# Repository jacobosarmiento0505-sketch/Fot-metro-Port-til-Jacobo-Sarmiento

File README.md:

# Fotómetro portátil para análisis de muestras

Proyecto del curso **Electrónica para Ingeniería Biomédica** (UDD) — diseño y
construcción de un fotómetro portátil de bajo costo, basado en un sensor de
color digital I2C y un microcontrolador ESP32, con pantalla OLED para
lectura directa de resultados.

## Estado del proyecto

- **Parte I** — propuesta, objetivos, requerimientos, diagrama de bloques y
  plan de pruebas: entregada (ver `docs/informes/`).
- **Parte II** — esquemático y layout de PCB en KiCad, lista de materiales
  (BOM) y archivos de fabricación: contenido de este repositorio.

## Resumen del hardware

El equipo mide la absorbancia/color de una muestra usando un sensor de
color RGB+Clear por I2C (**TCS34725**, módulo breakout HW-393), controlado
por una placa de desarrollo **ESP32**. Los resultados se muestran en una
pantalla **OLED SSD1306 (I2C, 128x64)**. Dos pulsadores permiten calibrar
con un blanco de referencia y disparar una medición. La alimentación es por
batería Li-Po, con carga/boost mediante un módulo TP4056 + convertidor
5V, regulado a 3.3V por el propio módulo ESP32.

> **Cambio de diseño respecto a la Parte I:** el front-end analógico
> original (fotodiodo BPW34 + amplificador operacional LM324) fue
> reemplazado por el sensor digital TCS34725, por sugerencia de los
> profesores del curso, para simplificar el diseño electrónico y de
> firmware. El detalle de este cambio está documentado en
> `docs/informes/`.

## Estructura del repositorio

```
.
├── README.md
├── LICENSE
├── docs/
│   ├── datasheets/      # hojas de datos de los componentes usados
│   ├── bitacora.md      # bitácora de avance del proyecto
│   └── informes/        # informes entregables (Parte I, Parte II)
├── electronica/
│   ├── kicad/           # proyecto KiCad: esquemático (.kicad_sch) y PCB (.kicad_pcb)
│   ├── libraries/       # librerías/símbolos o footprints propios (si los hay)
│   └── outputs/         # archivos de fabricación exportados (gerbers, STEP, BOM, PDFs)
├── firmware/            # firmware del ESP32 (Arduino/ESP-IDF)
└── software/            # software de apoyo (análisis de datos, scripts, etc.)
```

## Abrir el proyecto en KiCad

1. Instalar [KiCad 7](https://www.kicad.org/download/) (o superior).
2. Abrir `electronica/kicad/fotometro.kicad_pro`.
3. El esquemático (`fotometro.kicad_sch`) y el layout de PCB
   (`fotometro.kicad_pcb`) se abren desde ahí.

### Estado del enrutado de la PCB

La placa es de **una sola cara (B.Cu)**, pistas y espacios mínimos de
**0.8 mm**, con 4 orificios de montaje M3 (3.2 mm) — según lo pedido por el
Anexo 2 del enunciado. El esquemático está limpio (conectividad verificada
con `kicad-cli sch export netlist`) y la ubicación de todos los
footprints respeta los espaciamientos mínimos.

La placa se **rediseñó más compacta** a partir de la retroalimentación del
profesor: pasó de ~175 x 220 mm (38.500 mm²) a **~117 x 77 mm
(~9.000 mm²)**, cerca de la cuarta parte del área anterior. La distribución
se obtuvo con una búsqueda automática (recocido simulado sobre la ubicación y
rotación de cada componente, evaluando el ruteo real con el router A* del
proyecto). Las pistas se generaron con ese router y luego el estudiante las
**suavizó y ajustó a mano en KiCad** (pistas rectas y a 45°, sin zigzag); al final
se corrigieron unos pocos tramos de GND y VCC_5V para cumplir los 0,8 mm.

Resultado del enrutado (verificado sobre el archivo guardado):

- **Las 40 conexiones están ruteadas** — 0 pines sin conectar.
- **0 cortocircuitos** y **0 violaciones de separación**: el DRC con las reglas de
  0,8 mm de ancho y 0,8 mm de separación no marca errores.
- Todas las pistas están en **B.Cu** (0 en F.Cu), de 0,8 mm de ancho.
- Queda **1 advertencia** `copper_sliver` (B.Cu), documentada en el informe.
- Serigrafía con nombre del proyecto, versión (v2.0), equipo, integrantes,
  leyenda de pines de J1–J5 y pin 1 como pad cuadrado.

Cambio de huella: el interruptor SW1 pasó a `SW_Slide-03_Wuerth-WS-SLTV_10x2.5x6.4_P2.54mm`
(pines a 2.54 mm; el CK OS102011MS2Q anterior tenía pads a solo 2 mm entre sí, lo
que incumple por sí solo los 0.8 mm de separación). En el esquemático el pin 1 de SW1
es el contacto común (centro de la huella) y el pin 2 la salida.

## Archivos de fabricación

En `electronica/outputs/` se incluyen:

- `gerbers/` — Gerbers de las capas usadas + archivo de taladro (`.drl`)
- `fotometro_gerbers_y_taladro.zip` — Gerbers y taladro comprimidos
- `fotometro.step` — modelo 3D de la placa
- `fotometro_pcb.pdf` / `.svg` — vistas de la placa en vectorial
- `fotometro_pcb_cara_superior.png`, `fotometro_pcb_cara_inferior.png`,
  `fotometro_vista3d.png`, `fotometro_drc.png` — imágenes de las vistas y del DRC
- `fotometro_sch.pdf` / `fotometro_sch-1.png` — esquemático
- `BOM_fotometro.csv` — lista de materiales

Las bibliotecas propias están en `electronica/libraries/` y las hojas de datos
en `docs/datasheets/`. Los scripts que generan el esquemático y la PCB están en
`electronica/kicad/scripts/`.

## Autoría y uso de IA

Este repositorio fue preparado con ayuda de Claude (Anthropic) como asistente
de diseño: generación programática del esquemático y PCB en KiCad a partir
de la lista de materiales y topología de conexiones definidas por el
estudiante, además de la documentación. El detalle de este uso se describe
en `docs/informes/`, según lo pedido por el enunciado de la Parte II.

## Licencia

Este proyecto se publica bajo licencia MIT — ver [`LICENSE`](LICENSE).

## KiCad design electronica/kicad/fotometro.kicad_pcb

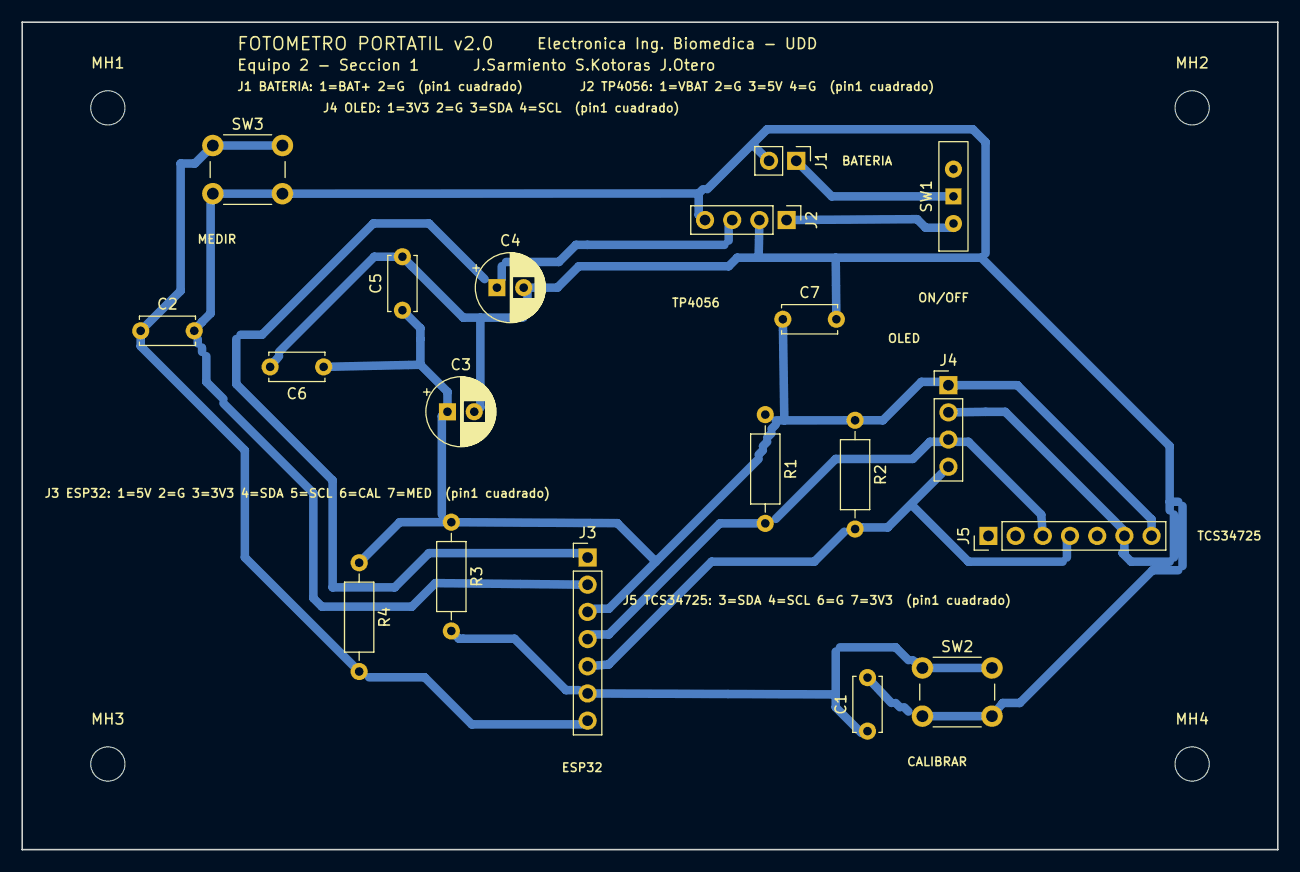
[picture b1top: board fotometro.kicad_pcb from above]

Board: 2 copper layers, 117.3 x 77.3 mm, 23 parts (0 on the bottom side), 9 nets.

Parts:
C1, C2, C5, C6, C7: 100nF; C_Disc_D5.0mm_W2.5mm_P5.00mm
C3, C4: 100uF; CP_Radial_D6.3mm_P2.50mm
J1: Bateria Li-Po; PinHeader_1x02_P2.54mm_Vertical
J2: TP4056+Boost5V; PinHeader_1x04_P2.54mm_Vertical
J3: ESP32; PinHeader_1x07_P2.54mm_Vertical
J4: OLED SSD1306; PinHeader_1x04_P2.54mm_Vertical
J5: TCS34725; PinHeader_1x07_P2.54mm_Vertical
MH1, MH2, MH3, MH4: MountingHole_3.2mm_M3
R1, R2: 4.7k; R_Axial_DIN0207_L6.3mm_D2.5mm_P10.16mm_Horizontal
R3, R4: 10k; R_Axial_DIN0207_L6.3mm_D2.5mm_P10.16mm_Horizontal
SW1: Interruptor encendido; SW_Slide-03_Wuerth-WS-SLTV_10x2.5x6.4_P2.54mm
SW2: CALIBRAR; SW_PUSH_6mm
SW3: MEDIR; SW_PUSH_6mm

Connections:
BAT_RAW: J1.1, SW1.1
GND: C1.2, C2.2, C3.2, C4.2, C5.2, C6.2, C7.2, J1.2, J2.2, J2.4, J3.2, J4.2, J5.6, SW2.2, SW3.2
GPIO_CAL: C1.1, J3.6, R3.2, SW2.1
GPIO_MED: C2.1, J3.7, R4.2, SW3.1
SCL: J3.5, J4.4, J5.4, R2.2
SDA: J3.4, J4.3, J5.3, R1.2
VBAT_SW: J2.1, SW1.2
VCC_3V3: C3.1, C5.1, C6.1, C7.1, J3.3, J4.1, J5.7, R1.1, R2.1, R3.1, R4.1
VCC_5V: C4.1, J2.3, J3.1

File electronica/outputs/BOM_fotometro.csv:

Referencia,Valor/Descripción corta,Footprint KiCad,Notas / función en el circuito,Cantidad
J1,Conector 2 pines (batería Li-po),Connector_PinHeader_2.54mm:PinHeader_1x02_P2.54mm_Vertical,Entrada de batería Li-Po (2S/1S según celda) -> BAT_RAW/GND,1
SW1,Interruptor deslizante SPDT (encendido),Button_Switch_THT:SW_Slide-03_Wuerth-WS-SLTV_10x2.5x6.4_P2.54mm,Interruptor general de encendido del equipo,1
J2,Conector 4 pines (módulo carga/regulador TP4056 + boost 5V),Connector_PinHeader_2.54mm:PinHeader_1x04_P2.54mm_Vertical,Interfaz al módulo TP4056 (carga Li-po) + boost a 5V,1
J3,Conector 7 pines (ESP32 dev board),Connector_PinHeader_2.54mm:PinHeader_1x07_P2.54mm_Vertical,"Interfaz a placa de desarrollo ESP32 (5V,GND,3V3,SDA,SCL,2x GPIO)",1
J4,Conector 4 pines (display OLED SSD1306 I2C),Connector_PinHeader_2.54mm:PinHeader_1x04_P2.54mm_Vertical,Interfaz a módulo OLED 128x64 I2C,1
J5,Conector 7 pines (sensor de color TCS34725 / HW-393),Connector_PinHeader_2.54mm:PinHeader_1x07_P2.54mm_Vertical,Interfaz al módulo sensor de color I2C TCS34725 (breakout HW-393),1
R1,Resistencia 4.7k,Resistor_THT:R_Axial_DIN0207_L6.3mm_D2.5mm_P10.16mm_Horizontal,Pull-up I2C SDA,1
R2,Resistencia 4.7k,Resistor_THT:R_Axial_DIN0207_L6.3mm_D2.5mm_P10.16mm_Horizontal,Pull-up I2C SCL,1
SW2,Pulsador táctil 6mm (CALIBRAR),Button_Switch_THT:SW_PUSH_6mm,Botón de calibración (blanco de referencia),1
R3,Resistencia 10k,Resistor_THT:R_Axial_DIN0207_L6.3mm_D2.5mm_P10.16mm_Horizontal,Pull-up botón CALIBRAR,1
C1,Capacitor cerámico 100nF,Capacitor_THT:C_Disc_D5.0mm_W2.5mm_P5.00mm,Antirrebote botón CALIBRAR,1
SW3,Pulsador táctil 6mm (MEDIR),Button_Switch_THT:SW_PUSH_6mm,Botón de inicio de medición,1
R4,Resistencia 10k,Resistor_THT:R_Axial_DIN0207_L6.3mm_D2.5mm_P10.16mm_Horizontal,Pull-up botón MEDIR,1
C2,Capacitor cerámico 100nF,Capacitor_THT:C_Disc_D5.0mm_W2.5mm_P5.00mm,Antirrebote botón MEDIR,1
C3,Capacitor electrolítico 100uF,Capacitor_THT:CP_Radial_D6.3mm_P2.50mm,"Desacople de bulto, riel 3V3",1
C4,Capacitor electrolítico 100uF,Capacitor_THT:CP_Radial_D6.3mm_P2.50mm,"Desacople de bulto, riel 5V",1
C5,Capacitor cerámico 100nF,Capacitor_THT:C_Disc_D5.0mm_W2.5mm_P5.00mm,Desacople local 3V3 (cerca ESP32),1
C6,Capacitor cerámico 100nF,Capacitor_THT:C_Disc_D5.0mm_W2.5mm_P5.00mm,Desacople local 3V3 (cerca OLED),1
C7,Capacitor cerámico 100nF,Capacitor_THT:C_Disc_D5.0mm_W2.5mm_P5.00mm,Desacople local 3V3 (cerca TCS34725),1

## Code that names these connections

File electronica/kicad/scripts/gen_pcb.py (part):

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    "SW1": (SS[0], SS[1], {"1": "BAT_RAW", "2": "VBAT_SW"}),
    "J2": (PH[0], PH[1] % 4, {"1": "VBAT_SW", "2": "GND", "3": "VCC_5V", "4": "GND"}),
    "J3": (PH[0], PH[1] % 7, {"1": "VCC_5V", "2": "GND", "3": "VCC_3V3", "4": "SDA",
                              "5": "SCL", "6": "GPIO_CAL", "7": "GPIO_MED"}),
    "J4": (PH[0], PH[1] % 4, {"1": "VCC_3V3", "2": "GND", "3": "SDA", "4": "SCL"}),
    "J5": (PH[0], PH[1] % 7, {"3": "SDA", "4": "SCL", "6": "GND", "7": "VCC_3V3"}),
    "R1": (RES[0], RES[1], {"1": "VCC_3V3", "2": "SDA"}),
    "R2": (RES[0], RES[1], {"1": "VCC_3V3", "2": "SCL"}),
    "SW2": (PB[0], PB[1], {"1": "GPIO_CAL", "2": "GND"}),
    "R3": (RES[0], RES[1], {"1": "VCC_3V3", "2": "GPIO_CAL"}),
    "C1": (CD[0], CD[1], {"1": "GPIO_CAL", "2": "GND"}),
    "SW3": (PB[0], PB[1], {"1": "GPIO_MED", "2": "GND"}),
    "R4": (RES[0], RES[1], {"1": "VCC_3V3", "2": "GPIO_MED"}),
    "C2": (CD[0], CD[1], {"1": "GPIO_MED", "2": "GND"}),
    "C3": (CP[0], CP[1], {"1": "VCC_3V3", "2": "GND"}),
    "C4": (CP[0], CP[1], {"1": "VCC_5V", "2": "GND"}),
    "C5": (CD[0], CD[1], {"1": "VCC_3V3", "2": "GND"}),
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FINAL_W, FINAL_H = 120.8, 79.6
FINAL_ORDER = ['VCC_3V3', 'BAT_RAW', 'VBAT_SW', 'VCC_5V', 'GPIO_MED', 'SDA', 'GND', 'GPIO_CAL', 'SCL']
PRIORITY = list(FINAL_ORDER)
ALLOW_RELAXED = True

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

SHORT = {"GND": "G", "VCC_3V3": "3V3", "VCC_5V": "5V", "VBAT_SW": "VBAT", "BAT_RAW": "BAT+",
         "GPIO_MED": "MED", "GPIO_CAL": "CAL", "SDA": "SDA", "SCL": "SCL"}
NAMES = {"J1": "BATERIA", "SW1": "ON/OFF", "J2": "TP4056", "J3": "ESP32", "J4": "OLED", "J5": "TCS34725",
         "SW2": "CALIBRAR", "SW3": "MEDIR"}
TITLE = ["FOTOMETRO PORTATIL v2.0", "Electronica Ing. Biomedica - UDD", "Equipo 2 - Seccion 1",
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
